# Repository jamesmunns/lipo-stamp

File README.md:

# LiPo Power Stamp

This is intended to be a small sized, general purpose LiPo charge controller with power path and a 3v3 regulator. Currently the targeted size is 0.7" by 0.7", or just under 18mm square. It is intended to be used with 3.7V nominal cells.

## Features

* TP4056 Charge Controller
    * 500mA charging current
    * Low voltage trickle charging
* Over/Under-voltage Protection
    * AP9101CK6 + FS8205
    * Disables cell on over/under charge
* Power Path
    * Provides power via USB when connected
    * 500mA max output (USB or Cell)
* Switchable 3v3 Regulator
    * Default off
    * 100mA+ output
* Resettable Polyfuse
    * For high current, direct battery applications (e.g. LEDs)
    * Max 2A continuous output

## Stamp v0.3.0

This is the current version of the board.

### Design Files

* [Schematic](./assets/stamp-schematic.pdf)
* [Layout](./assets/stamp-layout.pdf)

## Proto Version

The first version is a larger scale test board.

The [schematic](./assets/proto-schematic.pdf) is also available as PDF.

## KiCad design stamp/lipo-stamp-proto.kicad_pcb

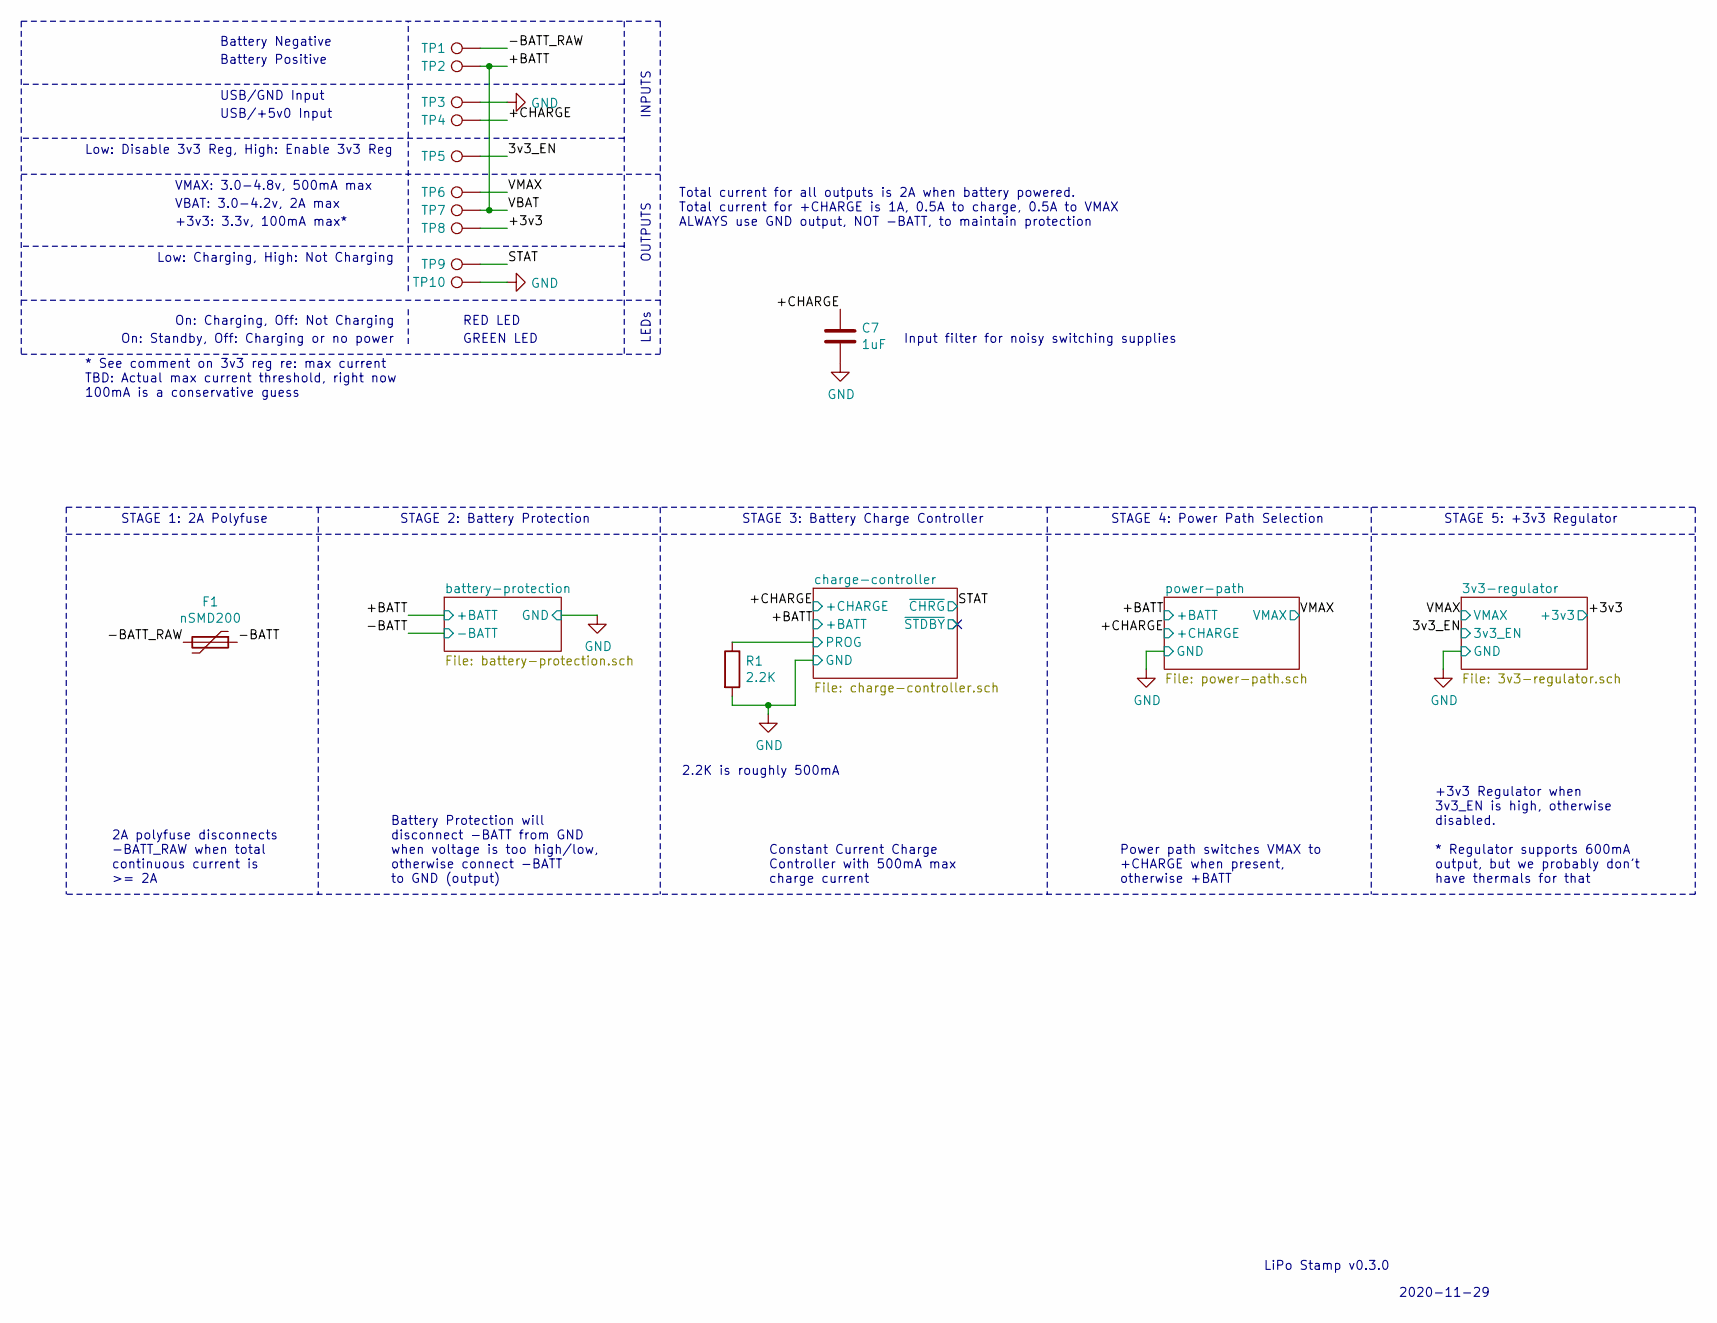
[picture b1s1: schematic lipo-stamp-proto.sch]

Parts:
C7: 1uF; C_0603_1608Metric
F1: nSMD200; Fuse_1206_3216Metric_Castellated
R1: 2.2K; R_0402_1005Metric
TP1, TP2, TP3, TP4, TP5, TP6, TP7, TP8, TP9, TP10: TestPoint; castellated-2-pin

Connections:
/3v3_EN: TP5.1; also elsewhere on the board
/+3v3: TP8.1; also elsewhere on the board
/+BATT: TP2.1, TP7.1; also elsewhere on the board
/+CHARGE: C7.1, TP4.1; also elsewhere on the board
/-BATT: F1.1; also elsewhere on the board
/-BATT_RAW: F1.2, TP1.1
/STAT: TP9.1; also elsewhere on the board
/VMAX: TP6.1; also elsewhere on the board
/charge-controller/PROG: R1.1; also elsewhere on the board
GND: C7.2, R1.2, TP3.1, TP10.1; also elsewhere on the board

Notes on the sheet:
2.2K is roughly 500mA
VMAX: 3.0-4.8v, 500mA max
VBAT: 3.0-4.2v, 2A max
+3v3: 3.3v, 100mA max*
Low: Charging, High: Not Charging
Low: Disable 3v3 Reg, High: Enable 3v3 Reg
USB/+5v0 Input
USB/GND Input
Battery Positive
Battery Negative
INPUTS
OUTPUTS
Total current for all outputs is 2A when battery powered. Total current for +CHARGE is 1A, 0.5A to charge, 0.5A to VMAX ALWAYS use GND output, NOT -BATT, to maintain protection
LiPo Stamp v0.3.0
2020-11-29
RED LED
GREEN LED
On: Charging, Off: Not Charging
On: Standby, Off: Charging or no power
LEDs
2A polyfuse disconnects -BATT_RAW when total continuous current is >= 2A
Battery Protection will disconnect -BATT from GND when voltage is too high/low, otherwise connect -BATT to GND (output)
Constant Current Charge Controller with 500mA max charge current
Power path switches VMAX to +CHARGE when present, otherwise +BATT
+3v3 Regulator when 3v3_EN is high, otherwise disabled. * Regulator supports 600mA output, but we probably don't have thermals for that
* See comment on 3v3 reg re: max current TBD: Actual max current threshold, right now 100mA is a conservative guess
STAGE 1: 2A Polyfuse
STAGE 2: Battery Protection
STAGE 3: Battery Charge Controller
STAGE 4: Power Path Selection
STAGE 5: +3v3 Regulator
Input filter for noisy switching supplies

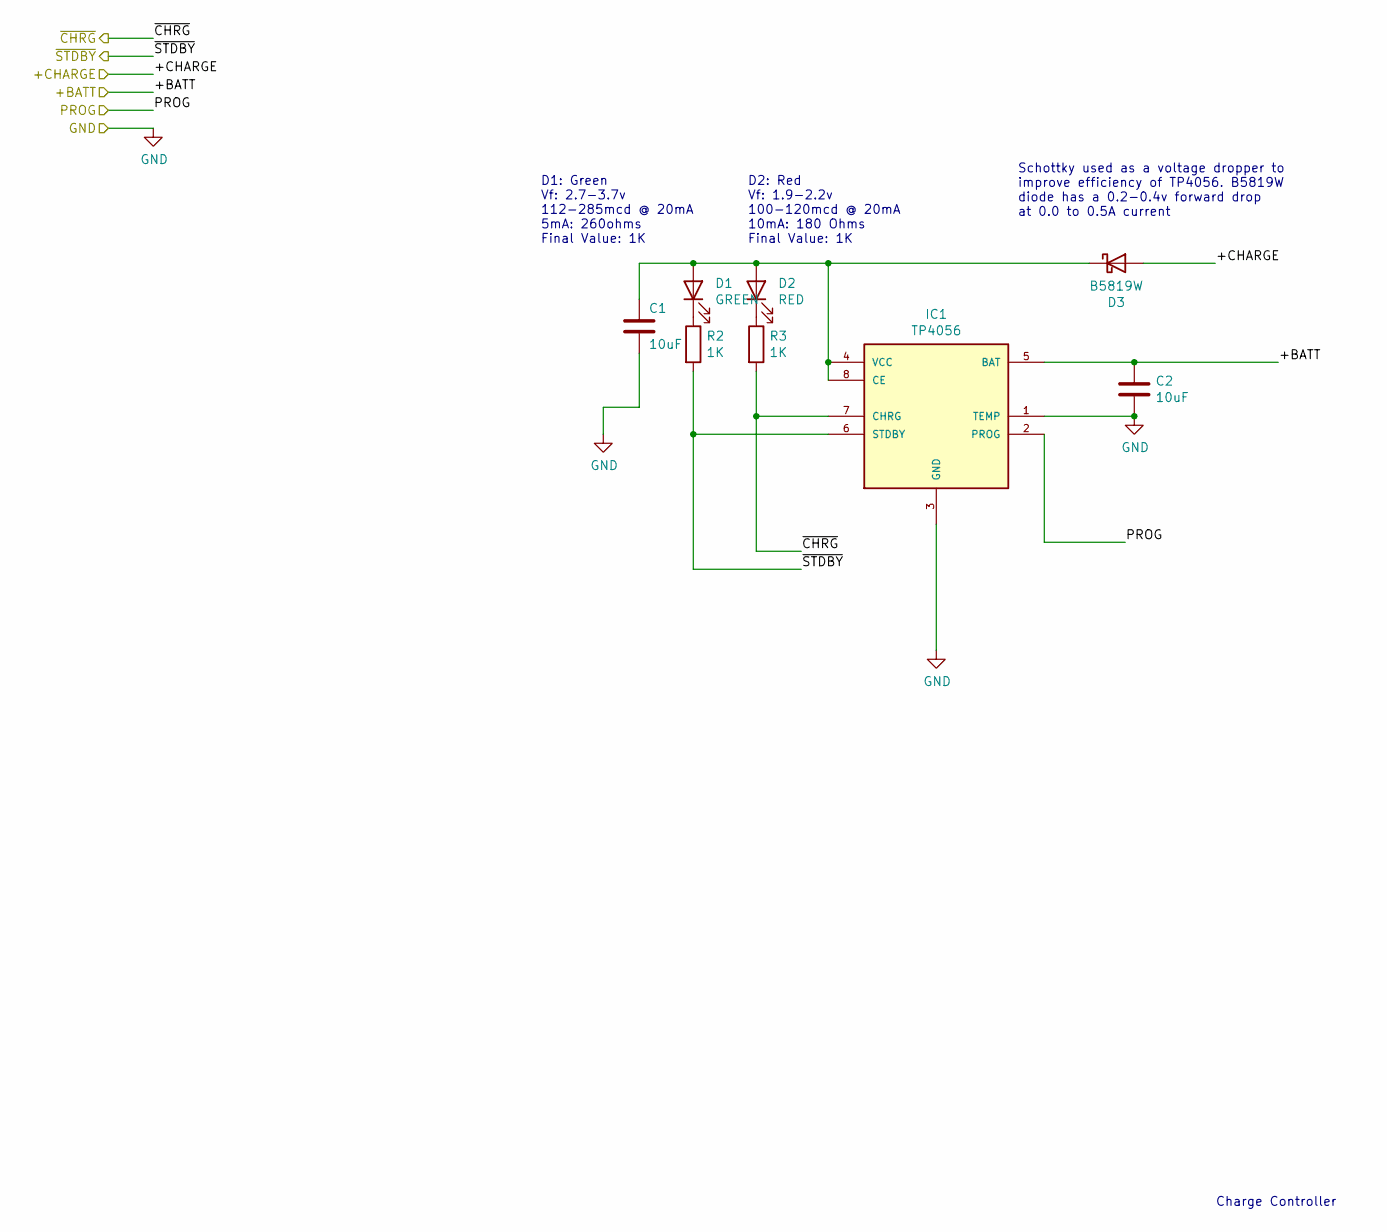
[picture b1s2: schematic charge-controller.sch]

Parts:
C1, C2: 10uF; C_0805_2012Metric
D1: GREEN; LED_0603_1608Metric
D2: RED; LED_0603_1608Metric
D3: B5819W; D_SOD-123
IC1: TP4056; SOP-8
R2, R3: 1K; R_0402_1005Metric

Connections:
/+BATT: C2.1, IC1.5 (BAT); also elsewhere on the board
/+CHARGE: D3.2 (A); also elsewhere on the board
/STAT: IC1.7 (CHRG), R3.2; also elsewhere on the board
/charge-controller/PROG: IC1.2 (PROG); also elsewhere on the board
/charge-controller/~STDBY: IC1.6 (STDBY), R2.2
GND: C1.2, C2.2, IC1.1 (TEMP), IC1.3 (GND); also elsewhere on the board
unnamed: C1.1, D1.2 (A), D2.2 (A), D3.1 (K), IC1.4 (VCC), IC1.8 (CE)
unnamed: D1.1 (K), R2.1
unnamed: D2.1 (K), R3.1

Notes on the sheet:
Charge Controller
Schottky used as a voltage dropper to improve efficiency of TP4056. B5819W diode has a 0.2-0.4v forward drop at 0.0 to 0.5A current
D1: Green Vf: 2.7-3.7v 112-285mcd @ 20mA 5mA: 260ohms Final Value: 1K
D2: Red Vf: 1.9-2.2v 100-120mcd @ 20mA 10mA: 180 Ohms Final Value: 1K

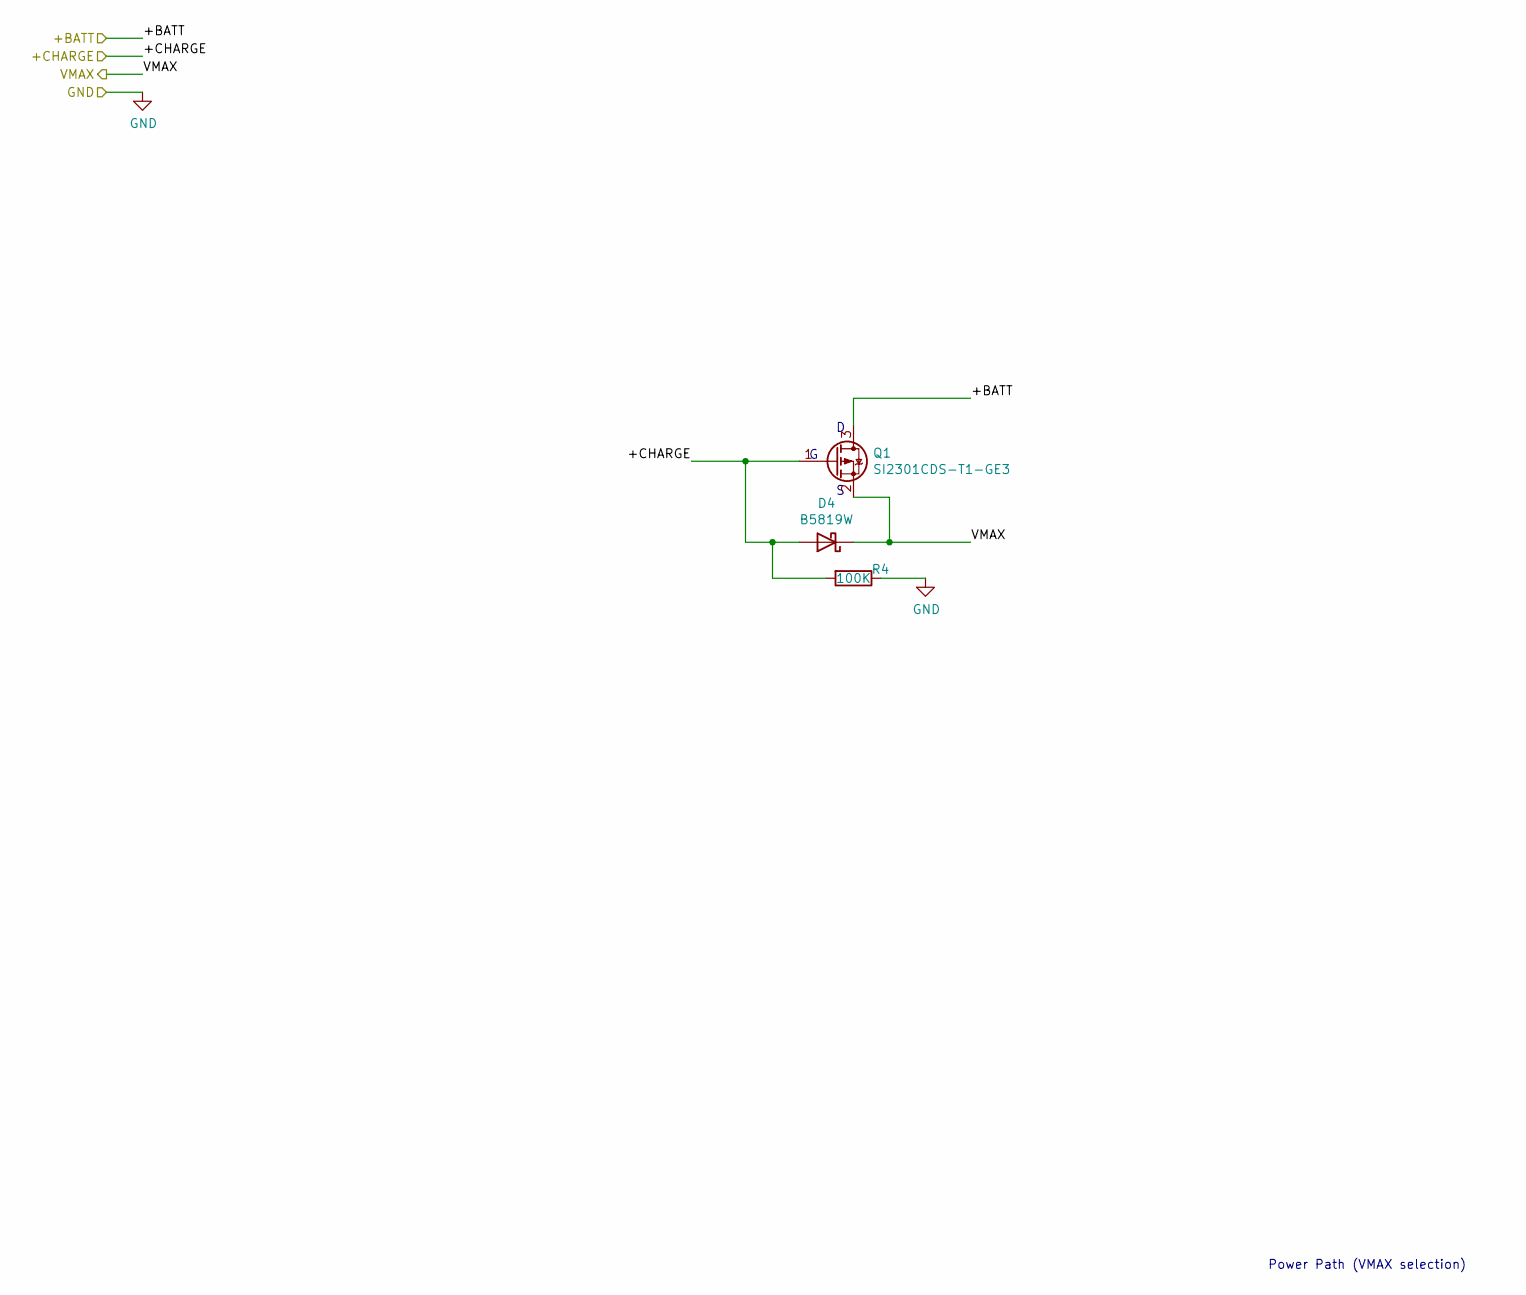
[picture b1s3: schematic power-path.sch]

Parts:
D4: B5819W; D_SOD-123
Q1: SI2301CDS-T1-GE3; SOT-23
R4: 100K; R_0402_1005Metric

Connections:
/+BATT: Q1.3 (D); also elsewhere on the board
/+CHARGE: D4.2 (A), Q1.1 (G), R4.2; also elsewhere on the board
/VMAX: D4.1 (K), Q1.2 (S); also elsewhere on the board
GND: R4.1; also elsewhere on the board

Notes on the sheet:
Power Path (VMAX selection)

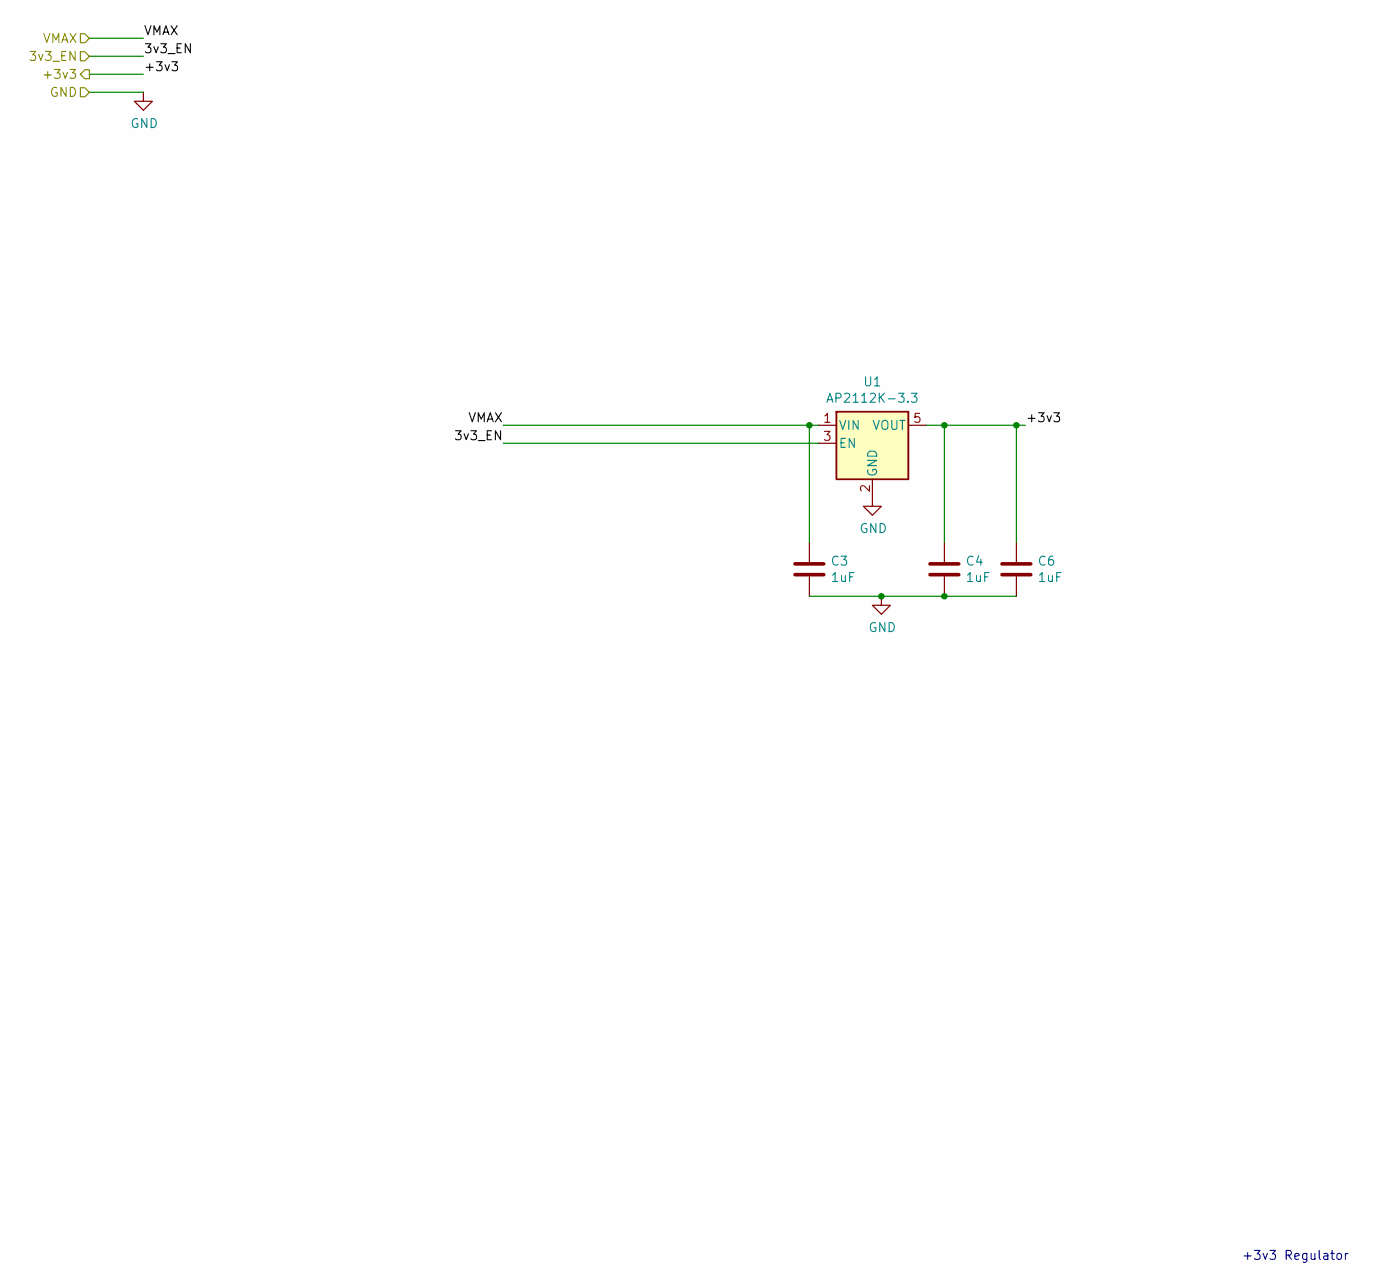
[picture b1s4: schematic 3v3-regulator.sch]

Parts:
C3, C4, C6: 1uF; C_0603_1608Metric
U1: AP2112K-3.3; SOT-23-5

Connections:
/3v3_EN: U1.3 (EN); also elsewhere on the board
/+3v3: C4.1, C6.1, U1.5 (VOUT); also elsewhere on the board
/VMAX: C3.1, U1.1 (VIN); also elsewhere on the board
GND: C3.2, C4.2, C6.2, U1.2 (GND); also elsewhere on the board

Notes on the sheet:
+3v3 Regulator

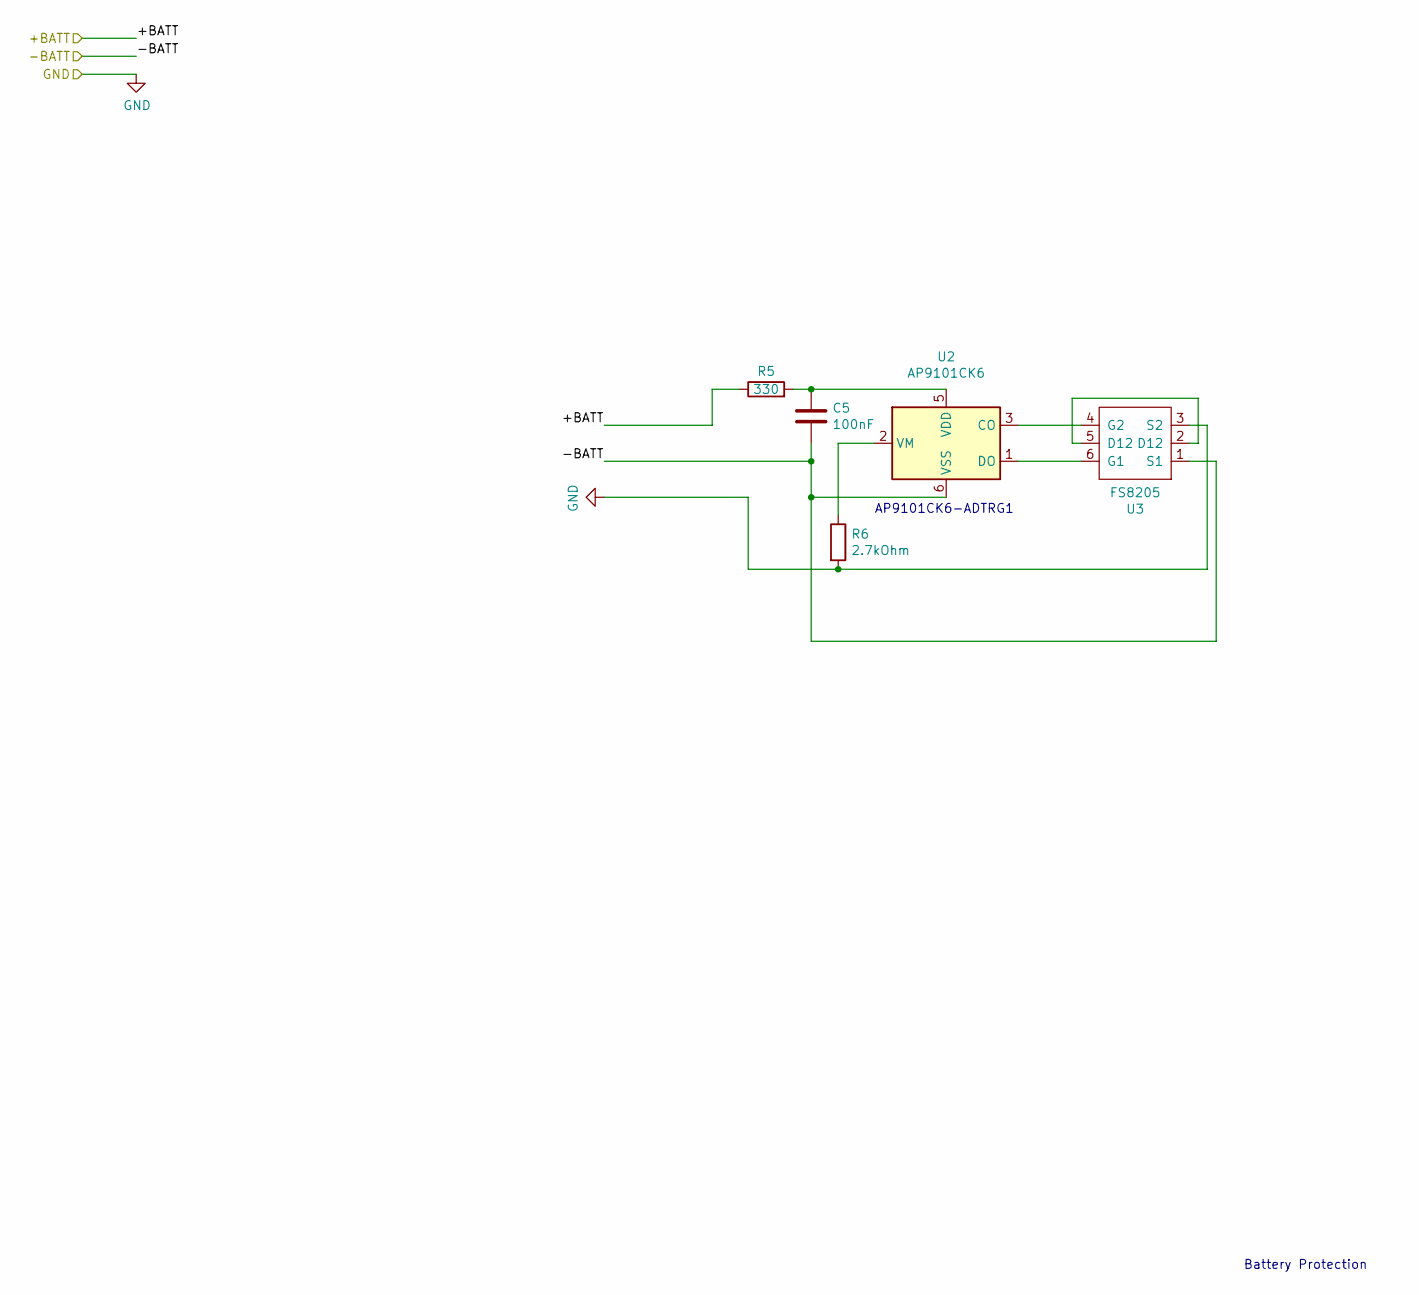
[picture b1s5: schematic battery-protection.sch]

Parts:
C5: 100nF; C_0603_1608Metric
R5: 330; R_0402_1005Metric
R6: 2.7kOhm; R_0603_1608Metric
U2: AP9101CK6; SOT-23-6
U3: FS8205; SOT-23-6

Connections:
/+BATT: R5.1; also elsewhere on the board
/-BATT: C5.2, U2.6 (VSS), U3.1 (S1); also elsewhere on the board
GND: R6.2, U3.3 (S2); also elsewhere on the board
unnamed: C5.1, R5.2, U2.5 (VDD)
unnamed: R6.1, U2.2 (VM)
unnamed: U2.1 (DO), U3.6 (G1)
unnamed: U2.3 (CO), U3.4 (G2)
unnamed: U3.2 (D12), U3.5 (D12)

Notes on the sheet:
AP9101CK6-ADTRG1
Battery Protection

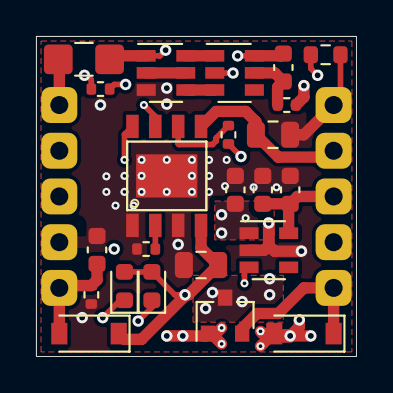
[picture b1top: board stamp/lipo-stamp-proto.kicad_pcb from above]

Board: 4 copper layers, 17.8 x 17.8 mm, 33 parts (0 on the bottom side), 19 nets.

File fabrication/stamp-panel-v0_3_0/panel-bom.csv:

"Id";"Designator";"Package";"Quantity";"Designation";"Supplier and ref";
1;"D1,D1,D1,D1,D1,D1,D1,D1,D1,D1,D1,D1,D1,D1,D1,D1";"LED_0603_1608Metric";16;"GREEN";;;
2;"D2,D2,D2,D2,D2,D2,D2,D2,D2,D2,D2,D2,D2,D2,D2,D2";"LED_0603_1608Metric";16;"RED";;;
3;"F1,F1,F1,F1,F1,F1,F1,F1,F1,F1,F1,F1,F1,F1,F1,F1";"Fuse_1206_3216Metric_Castellated";16;"2A Polyfuse";;;
4;"IC1,IC1,IC1,IC1,IC1,IC1,IC1,IC1,IC1,IC1,IC1,IC1,IC1,IC1,IC1,IC1";"SOP-8";16;"TP4056";;;
5;"Q1,Q1,Q1,Q1,Q1,Q1,Q1,Q1,Q1,Q1,Q1,Q1,Q1,Q1,Q1,Q1";"SOT-23";16;"SI2301CDS-T1-GE3";;;
6;"R1,R1,R1,R1,R1,R1,R1,R1,R1,R1,R1,R1,R1,R1,R1,R1";"R_0402_1005Metric";16;"2.2K";;;
7;"R2,R3,R2,R3,R2,R3,R2,R3,R2,R3,R2,R3,R2,R3,R2,R3,R2,R3,R2,R3,R2,R3,R2,R3,R2,R3,R2,R3,R2,R3,R2,R3";"R_0402_1005Metric";32;"1K";;;
8;"R4,R4,R4,R4,R4,R4,R4,R4,R4,R4,R4,R4,R4,R4,R4,R4";"R_0402_1005Metric";16;"100K";;;
9;"R5,R5,R5,R5,R5,R5,R5,R5,R5,R5,R5,R5,R5,R5,R5,R5";"R_0402_1005Metric";16;"330";;;
10;"TP1,TP2,TP3,TP4,TP5,TP6,TP7,TP8,TP9,TP10,TP1,TP2,TP3,TP4,TP5,TP6,TP7,TP8,TP9,TP10,TP1,TP2,TP3,TP4,TP5,TP6,TP7,TP8,TP9,TP10,TP1,TP2,TP3,TP4,TP5,TP6,TP7,TP8,TP9,TP10,TP1,TP2,TP3,TP4,TP5,TP6,TP7,TP8,TP9,TP10,TP1,TP2,TP3,TP4,TP5,TP6,TP7,TP8,TP9,TP10,TP1,TP2,TP3,TP4,TP5,TP6,TP7,TP8,TP9,TP10,TP1,TP2,TP3,TP4,TP5,TP6,TP7,TP8,TP9,TP10,TP1,TP2,TP3,TP4,TP5,TP6,TP7,TP8,TP9,TP10,TP1,TP2,TP3,TP4,TP5,TP6,TP7,TP8,TP9,TP10,TP1,TP2,TP3,TP4,TP5,TP6,TP7,TP8,TP9,TP10,TP1,TP2,TP3,TP4,TP5,TP6,TP7,TP8,TP9,TP10,TP1,TP2,TP3,TP4,TP5,TP6,TP7,TP8,TP9,TP10,TP1,TP2,TP3,TP4,TP5,TP6,TP7,TP8,TP9,TP10,TP1,TP2,TP3,TP4,TP5,TP6,TP7,TP8,TP9,TP10,TP1,TP2,TP3,TP4,TP5,TP6,TP7,TP8,TP9,TP10";"castellated-2-pin";160;"TestPoint";;;
11;"U1,U1,U1,U1,U1,U1,U1,U1,U1,U1,U1,U1,U1,U1,U1,U1";"SOT-23-5";16;"AP2112K-3.3";;;
12;"U2,U2,U2,U2,U2,U2,U2,U2,U2,U2,U2,U2,U2,U2,U2,U2";"SOT-23-6";16;"AP9101CK6";;;
13;"U3,U3,U3,U3,U3,U3,U3,U3,U3,U3,U3,U3,U3,U3,U3,U3";"SOT-23-6";16;"FS8205";;;
14;"D3,D4,D3,D4,D3,D4,D3,D4,D3,D4,D3,D4,D3,D4,D3,D4,D3,D4,D3,D4,D3,D4,D3,D4,D3,D4,D3,D4,D3,D4,D3,D4";"D_SOD-123";32;"D_Schottky";;;
15;"C1,C2,C1,C2,C1,C2,C1,C2,C1,C2,C1,C2,C1,C2,C1,C2,C1,C2,C1,C2,C1,C2,C1,C2,C1,C2,C1,C2,C1,C2,C1,C2";"C_0805_2012Metric";32;"10uF";;;
16;"C3,C4,C3,C4,C3,C4,C3,C4,C3,C4,C3,C4,C3,C4,C3,C4,C3,C4,C3,C4,C3,C4,C3,C4,C3,C4,C3,C4,C3,C4,C3,C4";"C_0603_1608Metric";32;"1uF";;;
17;"C5,C5,C5,C5,C5,C5,C5,C5,C5,C5,C5,C5,C5,C5,C5,C5";"C_0603_1608Metric";16;"100nF";;;
18;"R6,R6,R6,R6,R6,R6,R6,R6,R6,R6,R6,R6,R6,R6,R6,R6";"R_0603_1608Metric";16;"2.7kOhm";;;

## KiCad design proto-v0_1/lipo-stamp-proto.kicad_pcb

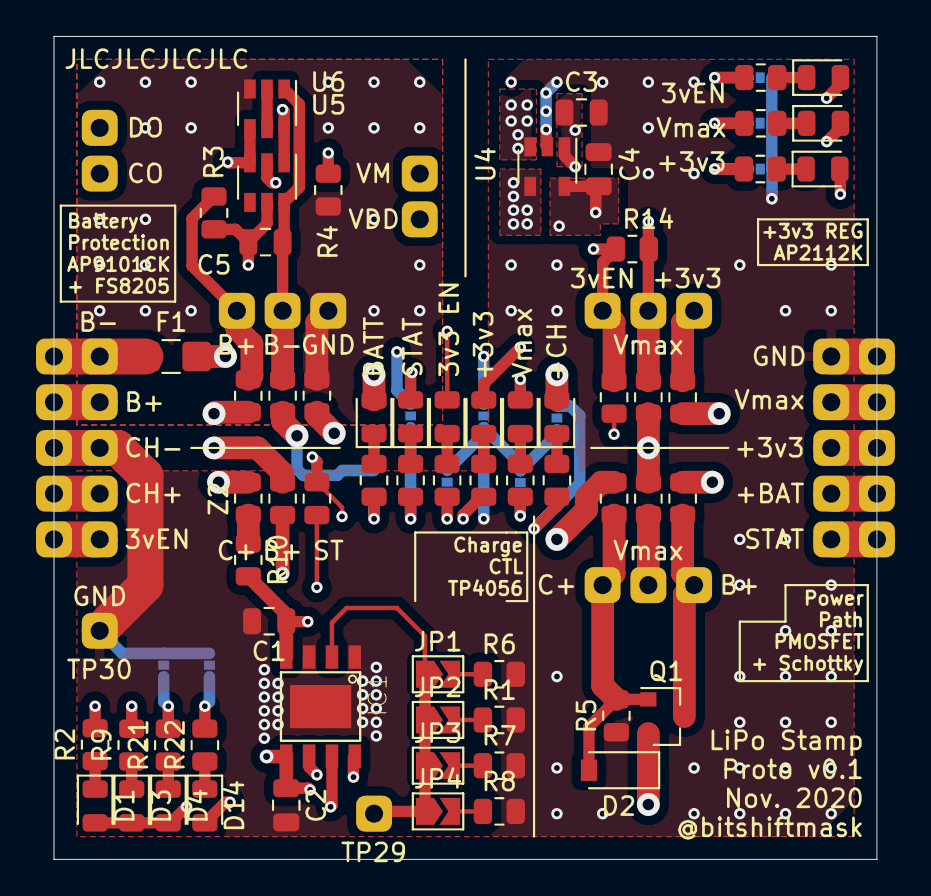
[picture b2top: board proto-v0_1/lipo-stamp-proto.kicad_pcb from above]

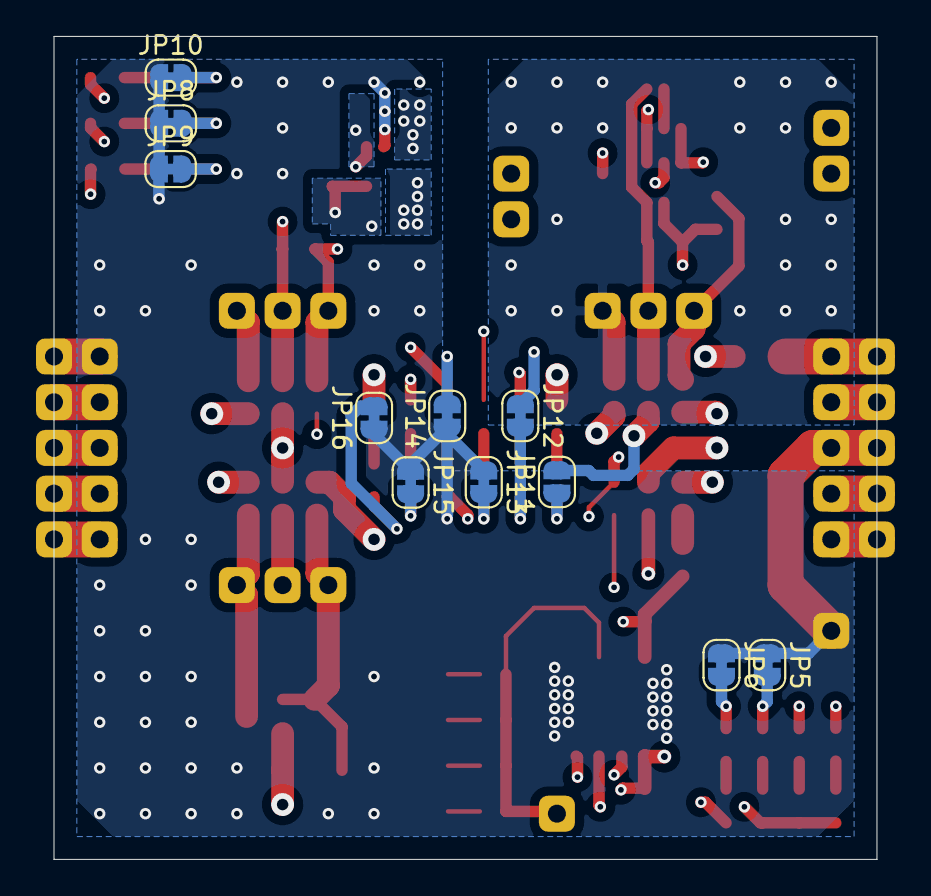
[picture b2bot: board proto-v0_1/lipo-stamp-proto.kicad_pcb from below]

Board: 4 copper layers, 45.7 x 45.7 mm, 109 parts (11 on the bottom side), 57 nets.

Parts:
C1, C2: 10uF; C_0805_2012Metric
C3, C4: 1uF; C_0805_2012Metric
C5: C; C_0805_2012Metric
D1, D3, D4, D5, D6, D7, D8, D9, D10, D11, D12, D13, D14: LED; LED_0805_2012Metric
D2: D_Schottky; D_SOD-123
F1: Polyfuse; Fuse_1206_3216Metric_Castellated
IC1: TP4056; SOP-8
JP1, JP2, JP3, JP4: SolderJumper_2_Open; SolderJumper-2_P1.3mm_Open_TrianglePad1.0x1.5mm
JP5, JP6, JP8, JP9, JP10, JP12, JP13, JP14, JP15, JP16: Jumper_NC_Small; SolderJumper-2_P1.3mm_Bridged_RoundedPad1.0x1.5mm
JP11: Jumper_NO_Small; SolderJumper-2_P1.3mm_Open_RoundedPad1.0x1.5mm
Q1: Q_PMOS_GSD; SOT-23
R1: 4K7; R_0805_2012Metric
R2, R9, R11, R12, R13, R15, R16, R17, R18, R19, R20, R21, R22: R; R_0805_2012Metric
R3: 330; R_0805_2012Metric
R4: 2.7kOhm; R_0805_2012Metric
R5: 100K; R_0805_2012Metric
R6, R14: 10K; R_0805_2012Metric
R7: 2K2; R_0805_2012Metric
R8: 1K2; R_0805_2012Metric
R10: 0.4; R_0805_2012Metric
TP1, TP2, TP3, TP4, TP5, TP6, TP7, TP8, TP9, TP10, TP11, TP12, TP13, TP14, TP15, TP16, TP17, TP18, TP19, TP20, TP21, TP22, TP23, TP24, TP25, TP26, TP27, TP28, TP29, TP30, TP34, TP35, TP36, TP37, TP38: TestPoint; castellated-2-pin
U4: AP2112K-3.3; SOT-23-5
U5: AP9101CK6; SOT-23-6
U6: FS8205; SOT-23-6
Z1, Z2, Z4, Z6, Z7, Z9, Z10, Z11, Z12, Z13, Z14, Z19: 0; R_0805_2012Metric

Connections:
/3V3_OUT: D11.2, TP7.1, TP17.1, Z12.1
/3V3_REG_EN: D10.2, TP8.1, TP18.1, Z11.2
/+BATT: D8.2, TP2.1, TP6.1, TP12.1, TP16.1, Z4.1, Z9.1, Z13.1
/+CHARGE: D13.2, TP4.1, TP14.1, Z1.2, Z2.2
/-BATT: F1.1, JP11.2, Z14.1
/-BATT_RAW: F1.2, TP1.1, TP11.1
/STAT_OUT: JP12.1, TP9.1, TP19.1, Z6.2
/VMAX_OUT: D9.2, D12.2, TP5.1, TP15.1, Z7.1, Z10.2
GND: C1.2, C2.2, C3.2, C4.2, IC1.1, IC1.3, JP5.1, JP6.1, JP8.1, JP9.1, JP10.1, JP13.1, JP14.1, JP15.1, JP16.1, R1.2, R5.1, R6.2, R7.2, R8.2, TP3.1, TP10.1, TP13.1, TP20.1, TP30.1, U4.2, Z19.1
unnamed: C1.1, D1.2, D3.2, D4.2, IC1.4, IC1.8, R10.2
unnamed: C2.1, D14.2, IC1.5, Z9.2
unnamed: C3.1, D5.2, R14.2, TP36.1, U4.1, Z10.1
unnamed: C4.1, D6.2, TP38.1, U4.5, Z12.2
unnamed: C5.1, R3.2, TP23.1, U5.5
unnamed: C5.2, TP21.1, U5.6, U6.1, Z14.2
unnamed: D1.1, R2.1
unnamed: D2.1, Q1.2, TP28.1, Z7.2
unnamed: D2.2, Q1.1, R5.2, TP26.1, Z1.1
unnamed: D3.1, R9.1
unnamed: D4.1, R21.1
unnamed: D5.1, R11.1
unnamed: D6.1, R12.1
unnamed: D7.1, R13.1
unnamed: D7.2, R14.1, TP37.1, U4.3, Z11.1
unnamed: D8.1, R15.1
unnamed: D9.1, R16.1
unnamed: D10.1, R17.1
unnamed: D11.1, R18.1
unnamed: D12.1, R19.1
unnamed: D13.1, R20.1
unnamed: D14.1, R22.1
unnamed: IC1.2, JP1.1, JP2.1, JP3.1, JP4.1, TP29.1
unnamed: IC1.6, R2.2
unnamed: IC1.7, R9.2, Z6.1
unnamed: JP1.2, R6.1
unnamed: JP2.2, R1.1
unnamed: JP3.2, R7.1
unnamed: JP4.2, R8.1
unnamed: JP5.2, R21.2
unnamed: JP6.2, R22.2
unnamed: JP8.2, R11.2
unnamed: JP9.2, R12.2
unnamed: JP10.2, R13.2
unnamed: JP11.1, R15.2
unnamed: JP12.2, R16.2
unnamed: JP13.2, R17.2
unnamed: JP14.2, R18.2
unnamed: JP15.2, R19.2
unnamed: JP16.2, R20.2
unnamed: Q1.3, TP27.1, Z4.2
unnamed: R3.1, TP35.1, Z13.2
unnamed: R4.1, TP22.1, U5.2
unnamed: R4.2, TP34.1, U6.3, Z19.2
unnamed: R10.1, Z2.1
unnamed: TP24.1, U5.3, U6.4
unnamed: TP25.1, U5.1, U6.6
unnamed: U6.2, U6.5

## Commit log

2020-11-21 Import from other project
2020-11-21 Initial import
2020-11-22 Going to start routing
2020-11-22 Passes DRC now
2020-11-22 Almost done, just needs back silkscreen
2020-11-22 Add schematic
2020-11-22 Add 2A polyfuse
2020-11-24 Polyfuse, pre-4056
2020-11-24 Rerouted TP4056, considering redoing
2020-11-29 Pre-rework
2020-11-29 Pre-review
2020-11-29 Add assets
2020-11-29 Update submodule
2020-11-29 Update readme with renders
2020-11-29 Move silkscreen layers
2020-11-29 Add fabrication outputs, not jlc corrected yet
2020-11-29 Update components, regenerate output
2020-11-29 Ignore zips
2020-11-29 Add panelization
2020-11-29 Add panelize script
2020-11-29 Remove accidental gerber output
2020-11-29 Update exports/screenshots
2020-11-29 Update render
2020-11-30 Address comments from Henrik
2020-11-30 Update panel fab
2020-11-30 Add features section
2020-11-30 Remove dead trace, increase return path via, add thermal spokes for ground
2020-11-30 Rework return path a bit more
2020-11-30 Update exports
2020-11-30 Break up big vias, use zones in inner layers for wider capacity
2020-11-30 Add more filter caps
2020-11-30 Ordered on 2020-11-30. v0.3.0 release.
2020-12-02 Update images
2020-12-26 Add app template, and some docs
2020-12-26 Basic skeleton, pins are still wrong
2021-01-14 Changed Battery to Cell and some other semantics
    Read the wiki (https://www.reddit.com/r/AskElectronics/wiki/batteries) of /r/batteries to learn more about batteries.
